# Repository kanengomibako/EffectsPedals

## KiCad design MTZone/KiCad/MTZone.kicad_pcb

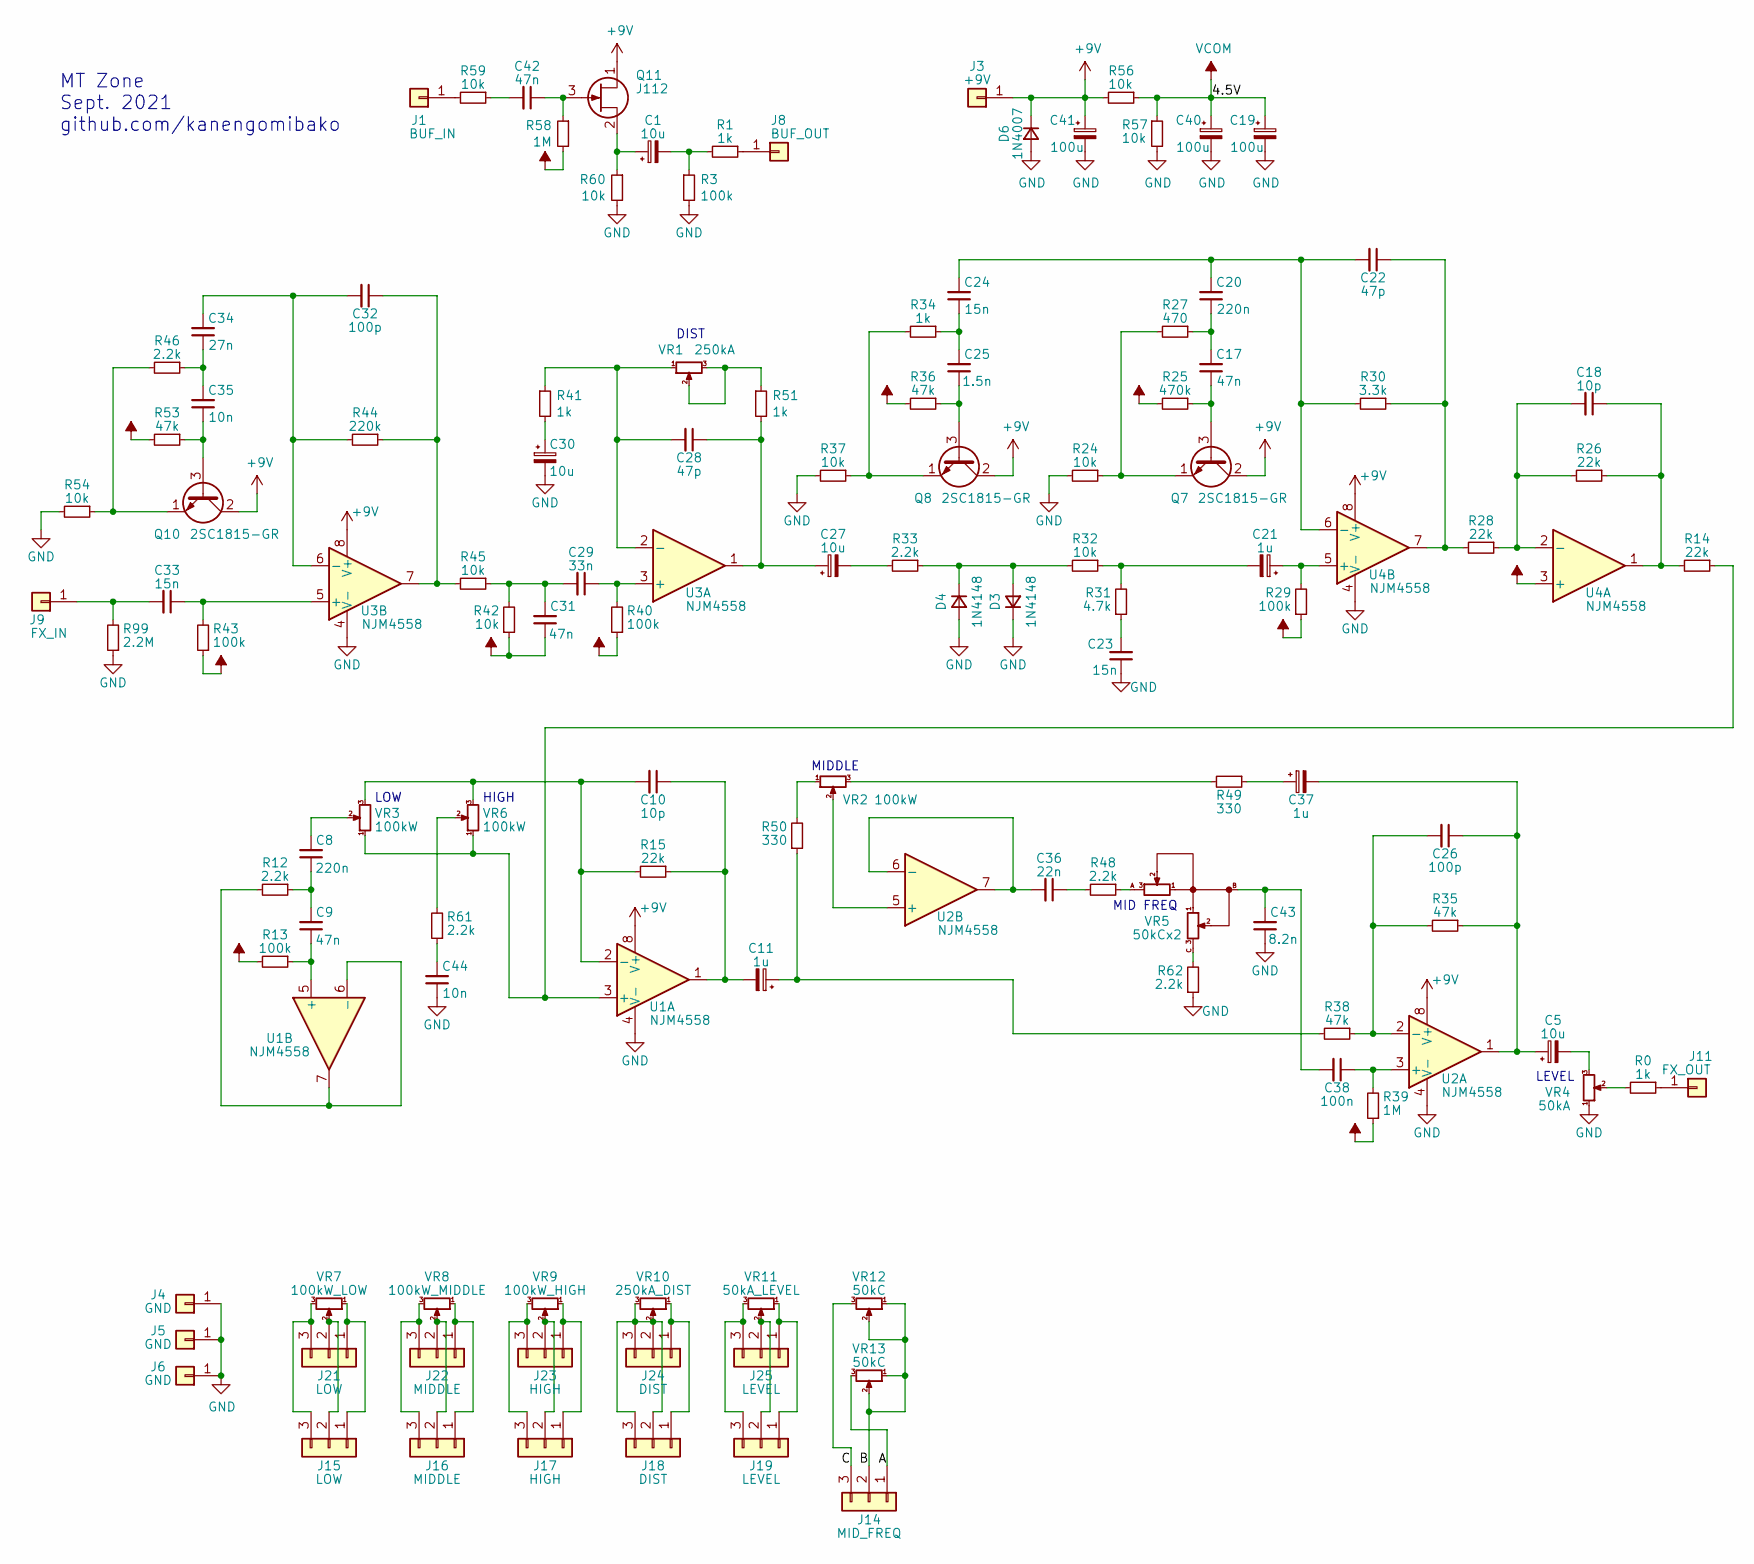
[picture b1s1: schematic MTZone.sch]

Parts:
C1, C5, C27, C30: 10u; my_C_D5.0mm_P2.50mm
C8, C20: 220n; my_C_Rect2_P5.00mm
C9, C17, C31, C42: 47n; my_C_Rect1_P5.00mm
C10, C18: 10p; my_C_Disc_P2.50mm
C11, C21, C37: 1u; my_C_D5.0mm_P2.50mm
C19, C40, C41: 100u; my_C_D5.0mm_P2.50mm
C22, C28: 47p; my_C_Disc_P2.50mm
C23, C24, C33: 15n; my_C_Rect1_P5.00mm
C25: 1.5n; my_C_Rect1_P5.00mm
C26, C32: 100p; my_C_Disc_P2.50mm
C29: 33n; my_C_Rect1_P5.00mm
C34: 27n; my_C_Rect1_P5.00mm
C35, C44: 10n; my_C_Rect1_P5.00mm
C36: 22n; my_C_Rect1_P5.00mm
C38: 100n; my_C_Rect1_P5.00mm
C43: 8.2n; my_C_Rect1_P5.00mm
D3, D4: 1N4148; my_D_P5.08mm_Horizontal
D6: 1N4007; my_D_P7.62mm
J1: BUF_IN; my_WirePad_0-8mmDrill
J3: +9V; my_WirePad_0-8mmDrill
J4, J5, J6: GND; my_WirePad_0-8mmDrill
J8: BUF_OUT; my_WirePad_0-8mmDrill
J9: FX_IN; my_WirePad_0-8mmDrill
J11: FX_OUT; my_WirePad_0-8mmDrill
J14: MID_FREQ; my_pot_5mm_smallPad
J15, J21: LOW; my_pot_5mm_smallPad
J16, J22: MIDDLE; my_pot_5mm_smallPad
J17, J23: HIGH; my_pot_5mm_smallPad
J18, J24: DIST; my_pot_5mm_smallPad
J19, J25: LEVEL; my_pot_5mm_smallPad
Q7, Q8, Q10: 2SC1815-GR; TO-92_Inline_Wide
Q11: J112; TO-92_Inline_Wide
R0, R1, R34, R41, R51: 1k; my_R_P7mm_Horizontal
R3, R13, R29, R40, R43: 100k; my_R_P7mm_Horizontal
R12, R33, R46, R48, R61, R62: 2.2k; my_R_P7mm_Horizontal
R14, R15, R26, R28: 22k; my_R_P7mm_Horizontal
R24, R32, R37, R42, R45, R54, R56, R57, R59, R60: 10k; my_R_P7mm_Horizontal
R25: 470k; my_R_P7mm_Horizontal
R27: 470; my_R_P7mm_Horizontal
R30: 3.3k; my_R_P7mm_Horizontal
R31: 4.7k; my_R_P7mm_Horizontal
R35, R36, R38, R53: 47k; my_R_P7mm_Horizontal
R39, R58: 1M; my_R_P7mm_Horizontal
R44: 220k; my_R_P7mm_Horizontal
R49, R50: 330; my_R_P7mm_Horizontal
R99: 2.2M; my_R_P7mm_Horizontal
U1, U2, U3, U4: NJM4558; DIP-8_W7.62mm
VR1: 250kA; my_pot_5mm
VR2, VR3, VR6: 100kW; my_pot_5mm
VR4: 50kA; my_pot_5mm
VR5: 50kCx2; my_pot_5mm
VR7: 100kW_LOW; my_pot_5mm_widePad
VR8: 100kW_MIDDLE; my_pot_5mm_widePad
VR9: 100kW_HIGH; my_pot_5mm_widePad
VR10: 250kA_DIST; my_pot_5mm_widePad
VR11: 50kA_LEVEL; my_pot_5mm_widePad
VR12, VR13: 50kC; my_pot_5mm_widePad

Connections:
+9V: C41.1, D6.1 (K), J3.1, Q7.2 (C), Q8.2 (C), Q10.2 (C), Q11.1 (D), R56.2, U1.8 (V+), U2.8 (V+), U3.8 (V+), U4.8 (V+)
/A: J14.1, VR13.3
/B: J14.2, VR12.1, VR12.2, VR13.1, VR13.2
/C: J14.3, VR12.3
GND: C19.2, C23.1, C30.2, C40.2, C41.2, C43.1, C44.1, D3.1 (K), D4.2 (A), D6.2 (A), J4.1, J5.1, J6.1, R3.2, R24.2, R37.2, R54.2, R57.2, R60.2, R62.1, R99.1, U1.4 (V-), U2.4 (V-), U3.4 (V-), U4.4 (V-), VR4.1
unnamed: C1.1, Q11.2 (S), R60.1
unnamed: C1.2, R1.2, R3.1
unnamed: C5.2, VR4.3
unnamed: C8.1, C9.2, R12.1
unnamed: C8.2, VR3.2
unnamed: C9.1, R13.1, U1.5 (+)
unnamed: C10.1, C11.2, R15.1, U1.1
unnamed: C10.2, R15.2, U1.2 (-), VR3.3, VR6.3
unnamed: C11.1, R38.2, R50.1
unnamed: C17.1, Q7.3 (B), R25.1
unnamed: C17.2, C20.1, R27.1
unnamed: C18.1, R14.2, R26.1, U4.1
unnamed: C18.2, R26.2, R28.1, U4.2 (-)
unnamed: C20.2, C22.2, C24.2, R30.2, U4.6 (-)
unnamed: C21.1, R29.2, U4.5 (+)
unnamed: C21.2, R31.2, R32.1
unnamed: C22.1, R28.2, R30.1, U4.7
unnamed: C23.2, R31.1
unnamed: C24.1, C25.2, R34.1
unnamed: C25.1, Q8.3 (B), R36.1
unnamed: C5.1, C26.1, C37.2, R35.1, U2.1
unnamed: C26.2, R35.2, R38.1, U2.2 (-)
unnamed: C27.1, C28.1, R51.2, U3.1
unnamed: C27.2, R33.2
unnamed: C28.2, R41.1, U3.2 (-), VR1.1
unnamed: C29.1, R40.2, U3.3 (+)
unnamed: C29.2, C31.2, R42.2, R45.1
unnamed: C30.1, R41.2
unnamed: C32.1, R44.1, R45.2, U3.7
unnamed: C32.2, C34.2, R44.2, U3.6 (-)
unnamed: C33.1, R43.2, U3.5 (+)
unnamed: C33.2, J9.1, R99.2
unnamed: C34.1, C35.2, R46.1
unnamed: C35.1, Q10.3 (B), R53.1
unnamed: C36.1, R48.2
unnamed: C36.2, U2.6 (-), U2.7
unnamed: C37.1, R49.1
unnamed: C38.1, R39.2, U2.3 (+)
unnamed: C38.2, C43.2, VR5.B
unnamed: C42.1, Q11.3 (G), R58.1
unnamed: C42.2, R59.1
unnamed: C44.2, R61.1
unnamed: D3.2 (A), D4.1 (K), R32.2, R33.1
unnamed: J1.1, R59.2
unnamed: J8.1, R1.1
unnamed: J11.1, R0.1
unnamed: J15.1, J21.1, VR7.1
unnamed: J15.2, J21.2, VR7.2
unnamed: J15.3, J21.3, VR7.3
unnamed: J16.1, J22.1, VR8.1
unnamed: J16.2, J22.2, VR8.2
unnamed: J16.3, J22.3, VR8.3
unnamed: J17.1, J23.1, VR9.1
unnamed: J17.2, J23.2, VR9.2
unnamed: J17.3, J23.3, VR9.3
unnamed: J18.1, J24.1, VR10.1
unnamed: J18.2, J18.3, J24.2, J24.3, VR10.2, VR10.3
unnamed: J19.1, J25.1, VR11.1
unnamed: J19.2, J25.2, VR11.2
unnamed: J19.3, J25.3, VR11.3
unnamed: Q7.1 (E), R24.1, R27.2
unnamed: Q8.1 (E), R34.2, R37.1
unnamed: Q10.1 (E), R46.2, R54.1
unnamed: R0.2, VR4.2
unnamed: R12.2, U1.6 (-), U1.7
unnamed: R14.1, U1.3 (+), VR3.1, VR6.1
unnamed: R48.1, VR5.A
unnamed: R49.2, VR2.3
unnamed: R50.2, VR2.1
unnamed: R51.1, VR1.2, VR1.3
unnamed: R61.2, VR6.2
unnamed: R62.2, VR5.C
unnamed: U2.5 (+), VR2.2
VCOM: C19.1, C31.1, C40.1, R13.2, R25.2, R29.1, R36.2, R39.1, R40.1, R42.1, R43.1, R53.2, R56.1, R57.1, R58.2, U4.3 (+)

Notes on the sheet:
MT Zone Sept. 2021 github.com/kanengomibako
HIGH
LOW
DIST
LEVEL
MIDDLE
MID FREQ

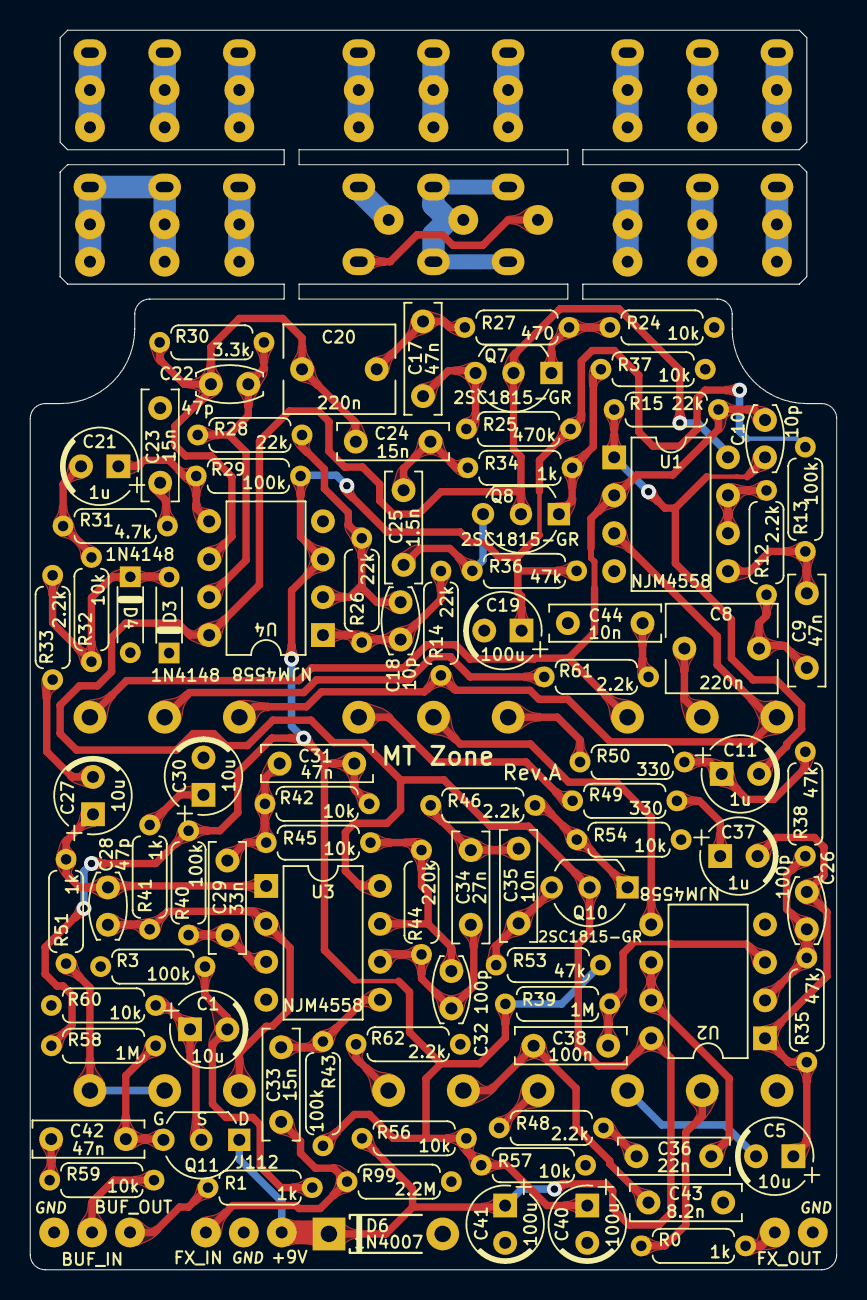
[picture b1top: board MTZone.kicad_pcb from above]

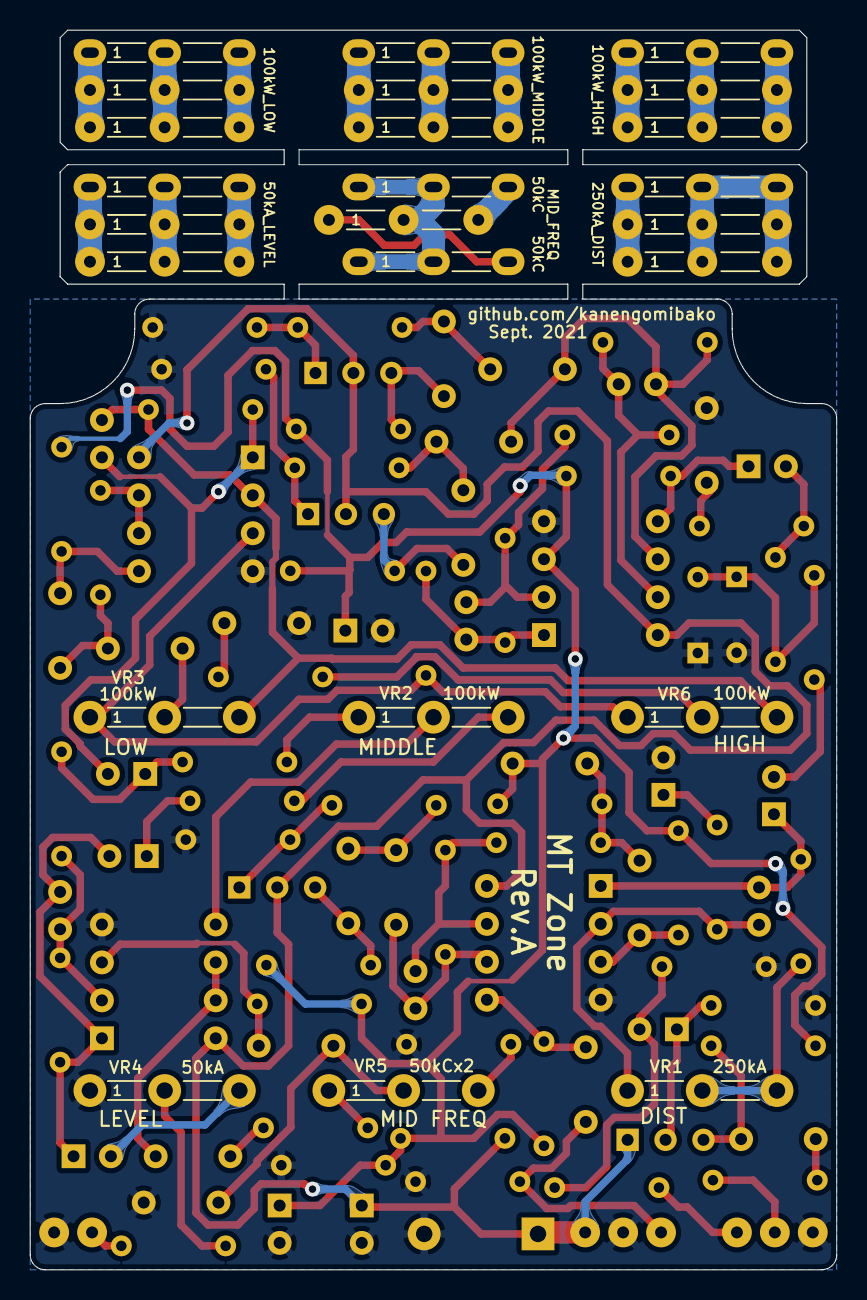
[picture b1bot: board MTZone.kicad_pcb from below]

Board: 2 copper layers, 54.0 x 83.0 mm, 120 parts (24 on the bottom side), 79 nets.

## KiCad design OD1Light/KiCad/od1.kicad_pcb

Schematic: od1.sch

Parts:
C1: 47n; C_0402_1005Metric
C2: 22n; C_0603_1608Metric
C3: 47p; C_0402_1005Metric
C4: 10n; C_0603_1608Metric
C5: 100n; C_0603_1608Metric
C6, C7, C8, C9: 10u; C_1206_3216Metric
D1, D2, D3, D4: MMSD4148; D_SOD-123
D5: LED; LED_D3.0mm
J1: VCC_IN_GND_OUT_LED-; PinHeader_1x05_P2.54mm_Vertical
R1, R8: 4.7k; R_0603_1608Metric
R2, R3: 1M; R_0603_1608Metric
R4: 33k; R_0603_1608Metric
R5: 18k; R_0603_1608Metric
R6: 1k; R_0603_1608Metric
R7: 100k; R_0603_1608Metric
RV1: 1MA; my_pot_5mm
RV2: 100kA; my_pot_5mm
U1: GS8632; MSOP-8_3x3mm_P0.65mm
U2: XC6221A332MR-G; SOT-23-5
U3: XC6221A182MR-G; SOT-23-5

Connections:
+1V8: C1.1, C4.1, C9.2, R3.2, RV2.1, U3.5 (OUT)
+3V3: C8.2, U1.8 (V+), U2.5 (OUT)
/INPUT: C2.2, J1.2, R2.1
/LED-: D5.1, J1.5
/OUTPUT: J1.4, R6.1, R7.1
/VCC: D4.2, J1.1, R8.2
GND: C7.1, C8.1, C9.1, J1.3, R2.2, R7.2, U1.4 (V-), U2.2 (GND), U3.2 (GND)
unnamed: C1.2, R1.1
unnamed: C2.1, R3.1, U1.5 (+)
unnamed: C3.1, D2.1, D3.2, R5.2, RV1.1, U1.7
unnamed: C3.2, D1.1, D2.2, R1.2, R4.2, U1.6 (-)
unnamed: C4.2, C5.2, R5.1
unnamed: C5.1, RV2.3
unnamed: C6.1, U1.1, U1.2 (-)
unnamed: C6.2, R6.2
unnamed: C7.2, D4.1, U2.1 (IN), U2.3 (EN), U3.1 (IN), U3.3 (EN)
unnamed: D1.2, D3.1
unnamed: D5.2, R8.1
unnamed: R4.1, RV1.2, RV1.3
unnamed: RV2.2, U1.3 (+)

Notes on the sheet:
BOSS OD-1 Over Drive (Light) May 2019 drugscore.blog.fc2.com
OVER DRIVE
LEVEL

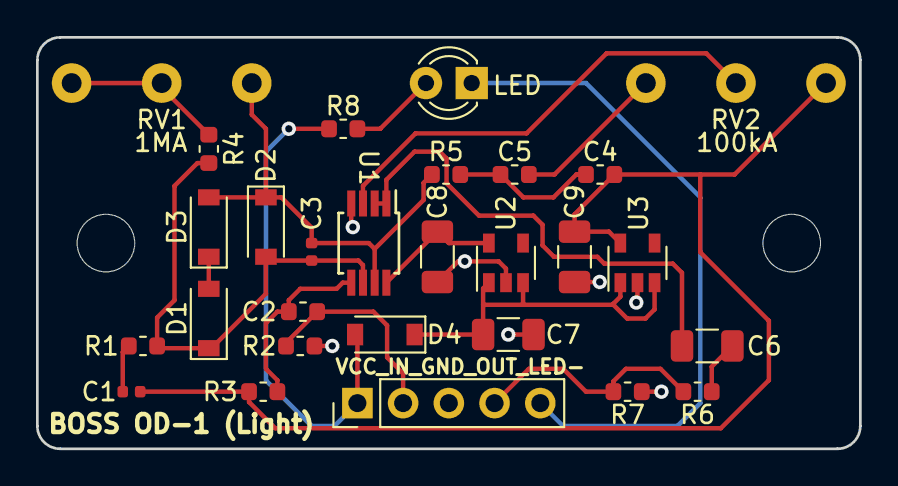
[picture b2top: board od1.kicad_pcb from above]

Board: 2 copper layers, 45.7 x 22.9 mm, 28 parts (0 on the bottom side), 20 nets.

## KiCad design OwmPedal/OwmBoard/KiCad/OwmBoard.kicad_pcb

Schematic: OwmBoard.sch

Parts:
C1, C3: 100n; my_C_3225(1210)_HandSoldering
C2, C4: 10n; my_C_1608(0603)_HandSoldering
C5, C6, C10, C11: 1n; my_C_1608(0603)_HandSoldering
C7, C8, C12, C13: 220p; my_C_1608(0603)_HandSoldering
C9, C14: 10u; my_CP_Elec_5
C15, C16, C17, C18: 20p; my_C_1608(0603)_HandSoldering
C19, C20: 2u2; my_C_2012(0805)_HandSoldering
C21, C41: 100u; my_C_D6.3mm_P2.50mm
C22, C23, C24, C25, C30, C31, C32, C33, C34, C35, C36, C37, C38, C39, C40, C42: 100n; my_C_1608(0603)_HandSoldering
C26, C27, C28, C29, C43: 10u; my_C_3216(1206)_HandSoldering
C44: (4u7); my_C_3216(1206)_HandSoldering
D1: LED; LED_D3.0mm
D2: 1N4007; D_DO-35_SOD27_P7.62mm_Horizontal
FB1: 330R; my_R_2012(0805)_HandSoldering
J1: LIN; my_SmallPad_0-8mmDrill
J2: RIN; my_SmallPad_0-8mmDrill
J3: LOUT; my_SmallPad_0-8mmDrill
J4: ROUT; my_SmallPad_0-8mmDrill
J5: C9(SDA); my_SmallPad_0-8mmDrill
J6: D2; my_SmallPad_0-8mmDrill
J7: C0; my_SmallPad_0-8mmDrill
J8: C1; my_SmallPad_0-8mmDrill
J9: C2; my_SmallPad_0-8mmDrill
J10: C3; my_SmallPad_0-8mmDrill
J11: C4; my_SmallPad_0-8mmDrill
J12: C5; my_SmallPad_0-8mmDrill
J13: C6; my_SmallPad_0-8mmDrill
J14: C7; my_SmallPad_0-8mmDrill
J16: C11; my_SmallPad_0-8mmDrill
J17, J18: 3.3VD; my_SmallPad_0-8mmDrill
J19, J20: DGND; my_SmallPad_0-8mmDrill
J21: A0; my_SmallPad_0-8mmDrill
J22: A1; my_SmallPad_0-8mmDrill
J23: A2; my_SmallPad_0-8mmDrill
J24: A3; my_SmallPad_0-8mmDrill
J25: A4; my_SmallPad_0-8mmDrill
J26: A5; my_SmallPad_0-8mmDrill
J27: A6; my_SmallPad_0-8mmDrill
J28: A7; my_SmallPad_0-8mmDrill
J29: A9; my_SmallPad_0-8mmDrill
J30: A10; my_SmallPad_0-8mmDrill
J31: A11; my_SmallPad_0-8mmDrill
J32: A12; my_SmallPad_0-8mmDrill
J33: SWD; my_SmallPad_0-8mmDrill
J34: SWC; my_SmallPad_0-8mmDrill
J35: B0; my_SmallPad_0-8mmDrill
J36: B1; my_SmallPad_0-8mmDrill
J37: B2; my_SmallPad_0-8mmDrill
J38: SWO; my_SmallPad_0-8mmDrill
J39: B4; my_SmallPad_0-8mmDrill
J40: B5; my_SmallPad_0-8mmDrill
J41: B6; my_SmallPad_0-8mmDrill
J42: B7; my_SmallPad_0-8mmDrill
J43: B8; my_SmallPad_0-8mmDrill
J44: B9; my_SmallPad_0-8mmDrill
J45: B10; my_SmallPad_0-8mmDrill
J46: B11; my_SmallPad_0-8mmDrill
J47: A15; my_SmallPad_0-8mmDrill
J48: A8(SCL); my_SmallPad_0-8mmDrill
J49, J51, J52: AGND; my_SmallPad_0-8mmDrill
J50: Vcc; my_SmallPad_0-8mmDrill
J53: NRST; my_SmallPad_0-8mmDrill
J54: C10; my_SmallPad_0-8mmDrill
J55: C12; my_SmallPad_0-8mmDrill
R1, R7, R38: 1k; my_R_2012(0805)_HandSoldering
R2, R8: 1M; my_R_1608(0603)_HandSoldering
R3, R4, R9, R10, R13, R14, R15, R16, R17, R18, R23, R24, R25, R26, R27, R28, R34, R36, R39, R41, R42: 10k; my_R_1608(0603)_HandSoldering
R5, R6, R11, R12, R21, R31: 100R; my_R_2012(0805)_HandSoldering
R19, R20, R29, R30: 2.2k; my_R_1608(0603)_HandSoldering
R22, R32, R43, R44: 100k; my_R_1608(0603)_HandSoldering
R33: 47k; my_R_1608(0603)_HandSoldering
R35, R45: 2.2M; my_R_1608(0603)_HandSoldering
R37, R40: (10k); my_R_1608(0603)_HandSoldering
TP1: ADC; my_TestPoint_1.2mm
TP2: LRCK; my_TestPoint_1.2mm
TP3: BCK; my_TestPoint_1.2mm
TP4: DAC; my_TestPoint_1.2mm
U1, U2, U3: OPA1678; SOIC-8_3.9x4.9mm_P1.27mm
U4: V4220M; my_SSOP-28_5.3x10.2mm_Pitch0.65mm
U5: STM32F405RGT6; my_LQFP-64_10x10_P0.5
U6, U8: 78L05; SOT-89-3
U7: 7805; my_TO-252-3
U9: 7833; my_TO-252-3
U10: 78L33; SOT-89-3
Y1: 12.288MHz; Crystal_SMD_HC49-SD
Y2: 8MHz; Crystal_SMD_HC49-SD

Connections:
+3V3: C29.1, C33.1, C36.1, C38.1, C39.1, C42.1, J17.1, J18.1, R37.1, R39.1, R40.1, U5.1, U5.13, U5.19, U5.32, U5.48, U5.64, U9.3
+5VA: C27.1, C31.1, U4.21, U7.3
+5VD: C28.1, C32.1, U4.6, U8.1 (OUT), U10.3 (IN)
+9V: C21.1, C22.1, C23.1, D2.1, FB1.2, J50.1, U6.3 (IN), U7.1
/+3.3VL: C35.1, C40.1, R34.1, U4.12, U4.13, U4.18, U10.1 (OUT)
/+5VAA: C26.1, C30.1, C34.1, C37.1, R41.2, U1.8 (V+), U2.8 (V+), U3.8 (V+), U6.1 (OUT)
/ADCDATA: R33.1, TP1.1, U4.8, U5.35
/BCK: TP3.1, U4.5, U5.34
/BIAS: C5.2, C6.2, C8.2, C10.2, C11.2, C13.2, C41.1, R2.2, R8.2, R17.2, R27.2, R41.1, R42.1, R43.1, R44.1, U1.3 (+), U2.3 (+)
/DACDATA: TP4.1, U4.9, U5.36
/LADC+: C2.1, R5.1, U4.20
/LADC-: C2.2, R6.1, U4.19
/LDAC+: R14.2, U4.25
/LDAC-: R13.2, U4.26
/LRCK: TP2.1, U4.4, U5.33
/RADC+: C4.1, R11.1, U4.17
/RADC-: C4.2, R12.1, U4.16
/RDAC+: R24.2, U4.24
/RDAC-: R23.2, U4.23
/RSTN: C43.1, R34.2, U4.27, U5.39
GNDA: C15.2, C16.2, C17.2, C18.2, C19.2, C20.2, C21.2, C22.2, C23.2, C24.2, C25.2, C26.2, C27.2, C28.2, C29.2, C30.2, C31.2, C32.2, C33.2, C34.2, C35.2, C36.2, C37.2, C38.2, C39.2, C40.2, C41.2, C42.2, C43.2, C44.2, D1.1, D2.2, J19.1, J20.1, J49.1, J51.1, J52.1, R22.2, R32.2, R33.2, R35.2, R36.2, R42.2, R43.2, R44.2, R45.2, U1.4 (V-), U2.4 (V-), U3.4 (V-), U4.1, U4.7, U4.10, U4.11, U4.14, U4.15, U4.22, U4.28, U5.12, U5.18, U5.63, U6.2 (GND), U7.2, U8.2 (GND), U9.2, U10.2 (GND)
unnamed: C1.1, R1.2
unnamed: C1.2, J1.1, R35.1
unnamed: C3.1, R7.2
unnamed: C3.2, J2.1, R45.1
unnamed: C5.1, R15.1, R18.2, R19.2
unnamed: C6.1, R16.1, R17.1, R20.2
unnamed: C7.1, C9.1, R18.1, U3.1
unnamed: C7.2, R19.1, U3.2 (-)
unnamed: C8.1, R20.1, U3.3 (+)
unnamed: C9.2, R21.2
unnamed: C10.1, R25.1, R28.2, R29.2
unnamed: C11.1, R26.1, R27.1, R30.2
unnamed: C12.1, C14.1, R28.1, U3.7
unnamed: C12.2, R29.1, U3.6 (-)
unnamed: C13.1, R30.1, U3.5 (+)
unnamed: C14.2, R31.2
unnamed: C15.1, U4.3, Y1.1
unnamed: C16.1, U4.2, Y1.2
unnamed: C17.1, U5.6, Y2.1
unnamed: C18.1, U5.5, Y2.2
unnamed: C19.1, U5.31
unnamed: C20.1, U5.47
unnamed: C24.1, C25.1, FB1.1, U8.3 (IN), U9.1
unnamed: C44.1, J46.1, U5.30
unnamed: D1.2, R38.1
unnamed: J3.1, R21.1, R22.1
unnamed: J4.1, R31.1, R32.1
unnamed: J5.1, R37.2, U5.40
unnamed: J6.1, U5.54
unnamed: J7.1, U5.8
unnamed: J8.1, U5.9
unnamed: J9.1, U5.10
unnamed: J10.1, U5.11
unnamed: J11.1, U5.24
unnamed: J12.1, U5.25
unnamed: J13.1, U5.37
unnamed: J14.1, U5.38
unnamed: J16.1, U5.52
unnamed: J21.1, U5.14
unnamed: J22.1, U5.15
unnamed: J23.1, U5.16
unnamed: J24.1, U5.17
unnamed: J25.1, U5.20
unnamed: J26.1, U5.21
unnamed: J27.1, U5.22
unnamed: J28.1, U5.23
unnamed: J29.1, U5.42
unnamed: J30.1, U5.43
unnamed: J31.1, U5.44
unnamed: J32.1, U5.45
unnamed: J33.1, U5.46
unnamed: J34.1, U5.49
unnamed: J35.1, U5.26
unnamed: J36.1, U5.27
unnamed: J37.1, U5.28
unnamed: J38.1, U5.55
unnamed: J39.1, U5.56
unnamed: J40.1, U5.57
unnamed: J41.1, U5.58
unnamed: J42.1, U5.59
unnamed: J43.1, U5.61
unnamed: J44.1, U5.62
unnamed: J45.1, U5.29
unnamed: J47.1, U5.50
unnamed: J48.1, R40.2, U5.41
unnamed: J53.1, R39.2, U5.7
unnamed: J54.1, U5.51
unnamed: J55.1, U5.53
unnamed: R1.1, R2.1, U1.5 (+)
unnamed: R3.1, R5.2, U1.6 (-), U1.7
unnamed: R3.2, R4.2, U1.2 (-)
unnamed: R4.1, R6.2, U1.1
unnamed: R7.1, R8.1, U2.5 (+)
unnamed: R10.1, R12.2, U2.1
unnamed: R9.2, R10.2, U2.2 (-)
unnamed: R9.1, R11.2, U2.6 (-), U2.7
unnamed: R13.1, R15.2
unnamed: R14.1, R16.2
unnamed: R23.1, R25.2
unnamed: R24.1, R26.2
unnamed: R36.1, U5.60
unnamed: R38.2, U5.2

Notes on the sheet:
Owm Board Rev.C May 2019 drugscore.blog.fc2.com

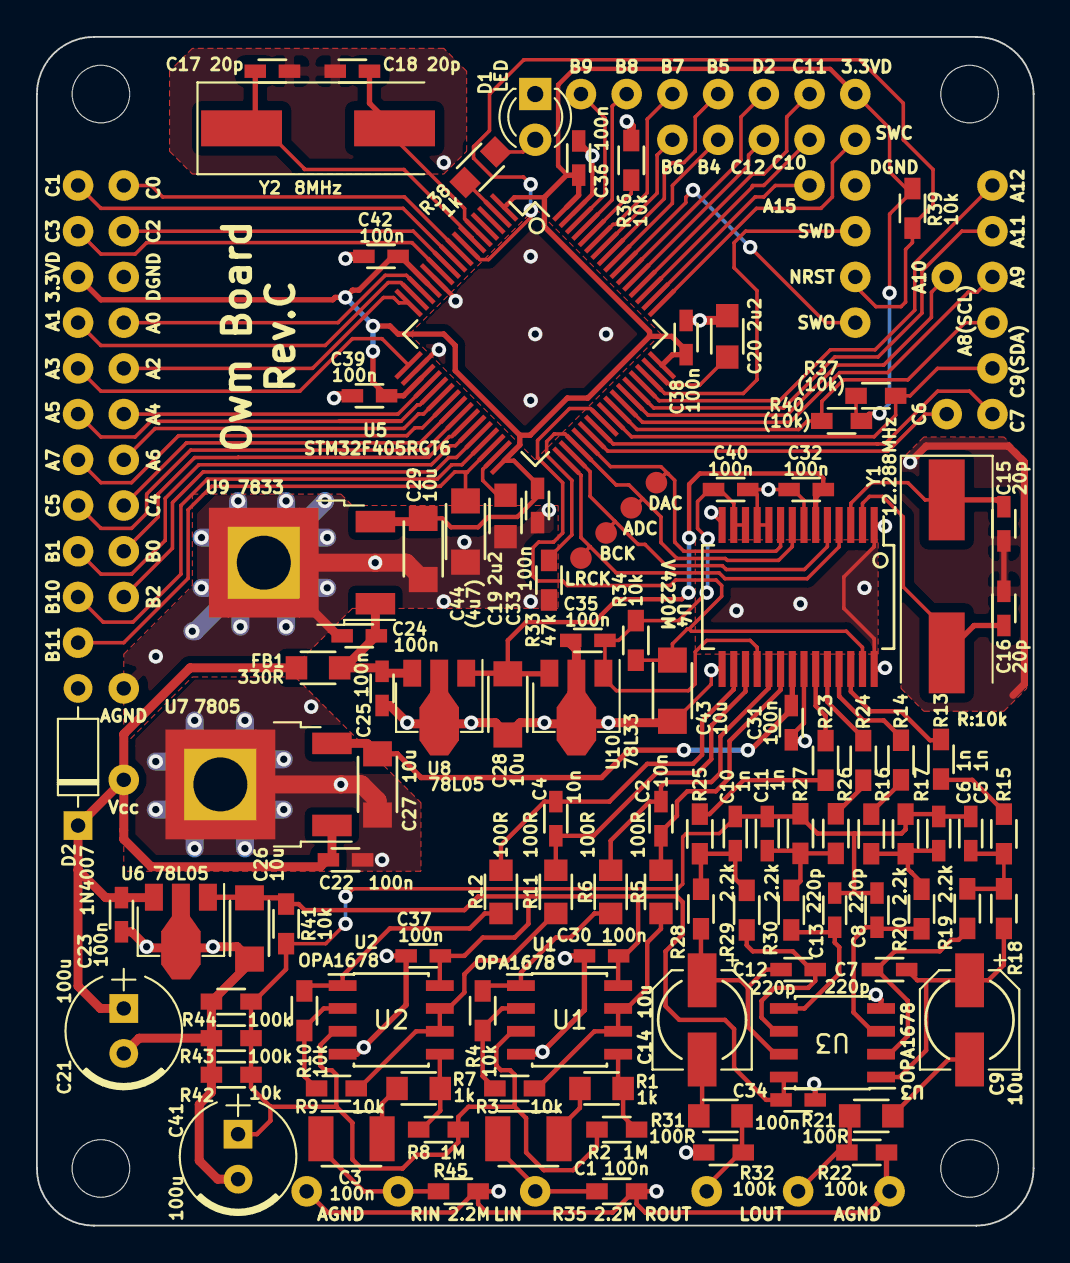
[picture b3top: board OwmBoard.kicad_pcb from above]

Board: 2 copper layers, 55.4 x 66.0 mm, 162 parts (0 on the bottom side), 103 nets.

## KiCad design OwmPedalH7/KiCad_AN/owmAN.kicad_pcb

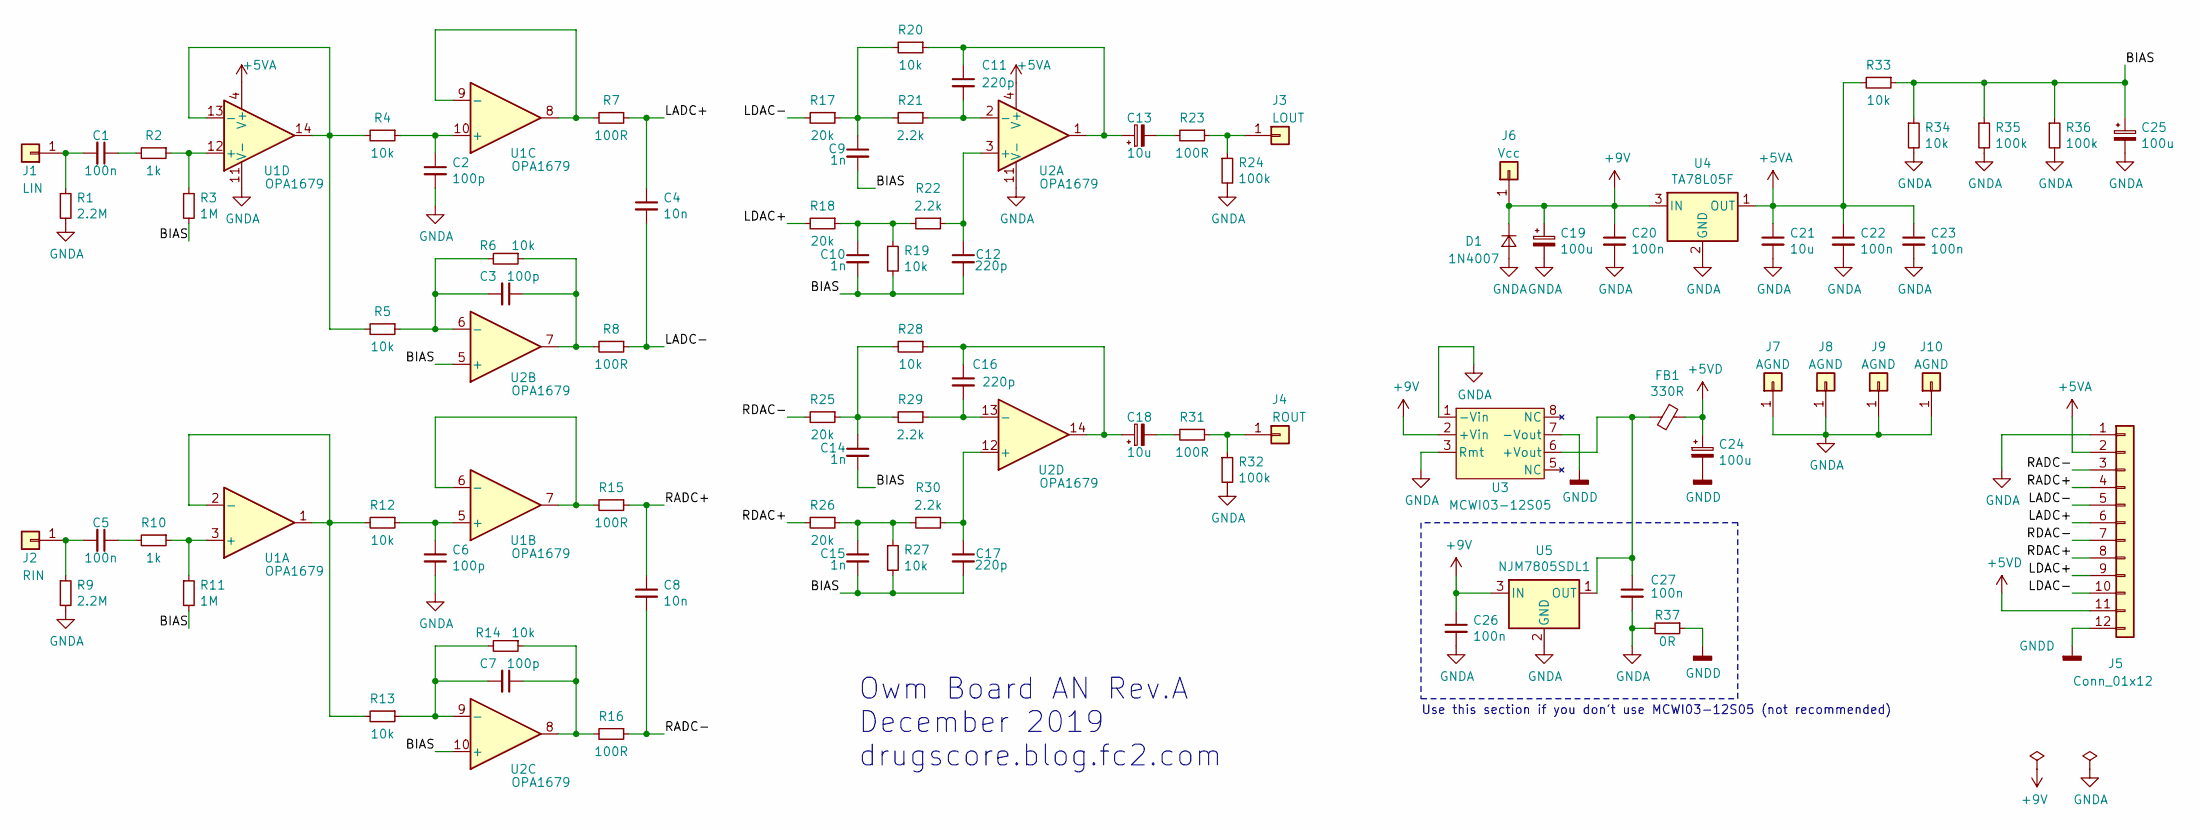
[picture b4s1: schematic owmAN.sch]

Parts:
C1, C5: 100n; my_C_3225(1210)_HandSoldering
C2, C3, C6, C7: 100p; my_C_1608(0603)_HandSoldering
C4, C8: 10n; my_C_1608(0603)_HandSoldering
C9, C10, C14, C15: 1n; my_C_1608(0603)_HandSoldering
C11, C12, C16, C17: 220p; my_C_1608(0603)_HandSoldering
C13, C18: 10u; my_C_Elec_5
C19, C24, C25: 100u; my_C_D6.3mm_P2.50mm
C20, C22, C23, C26, C27: 100n; my_C_1608(0603)_HandSoldering
C21: 10u; my_C_3216(1206)_HandSoldering
D1: 1N4007; D_DO-35_SOD27_P7.62mm_Horizontal
FB1: 330R; my_R_2012(0805)_HandSoldering
J1: LIN; my_SmallPad_0-8mmDrill
J2: RIN; my_SmallPad_0-8mmDrill
J3: LOUT; my_SmallPad_0-8mmDrill
J4: ROUT; my_SmallPad_0-8mmDrill
J5: Conn_01x12; PinHeader_1x12_P2.54mm_Vertical
J6: Vcc; my_SmallPad_0-8mmDrill
J7, J8, J9, J10: AGND; my_SmallPad_0-8mmDrill
R1, R9: 2.2M; my_R_1608(0603)_HandSoldering
R2, R10: 1k; my_R_2012(0805)_HandSoldering
R3, R11: 1M; my_R_1608(0603)_HandSoldering
R4, R5, R6, R12, R13, R14, R19, R20, R27, R28, R33, R34: 10k; my_R_1608(0603)_HandSoldering
R7, R8, R15, R16, R23, R31: 100R; my_R_2012(0805)_HandSoldering
R17, R18, R25, R26: 20k; my_R_1608(0603)_HandSoldering
R21, R22, R29, R30: 2.2k; my_R_1608(0603)_HandSoldering
R24, R32, R35, R36: 100k; my_R_1608(0603)_HandSoldering
R37: 0R; my_R_P7.62mm_Horizontal
U1, U2: OPA1679; my_TSSOP-14
U3: MCWI03-12S05
U4: TA78L05F; SOT-89-3
U5: NJM7805SDL1; my_TO-252-3

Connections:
+5VA: C21.1, C22.1, C23.1, J5.2, R33.2, U1.4 (V+), U2.4 (V+), U4.1 (OUT)
+5VD: C24.1, FB1.1, J5.11
+9V: C19.1, C20.1, C26.1, D1.1 (K), J6.1, U3.2 (+Vin), U4.3 (IN), U5.3 (IN)
/BIAS: C9.2, C10.2, C12.2, C14.2, C15.2, C17.2, C25.1, R3.2, R11.2, R19.2, R27.2, R33.1, R34.1, R35.1, R36.1, U2.5 (+), U2.10 (+)
/LADC+: C4.1, J5.6, R7.1
/LADC-: C4.2, J5.5, R8.1
/LDAC+: J5.9, R18.2
/LDAC-: J5.10, R17.2
/RADC+: C8.1, J5.4, R15.1
/RADC-: C8.2, J5.3, R16.1
/RDAC+: J5.8, R26.2
/RDAC-: J5.7, R25.2
GNDA: C2.2, C6.2, C19.2, C20.2, C21.2, C22.2, C23.2, C25.2, C26.2, C27.2, D1.2 (A), J5.1, J7.1, J8.1, J9.1, J10.1, R1.2, R9.2, R24.2, R32.2, R34.2, R35.2, R36.2, R37.2, U1.11 (V-), U2.11 (V-), U3.1 (-Vin), U3.3 (Rmt), U4.2 (GND), U5.2 (GND)
GNDD: C24.2, J5.12, R37.1, U3.7 (-Vout)
unnamed: C1.1, R2.2
unnamed: C1.2, J1.1, R1.1
unnamed: C2.1, R4.1, U1.10 (+)
unnamed: C3.1, R6.1, R8.2, U2.7
unnamed: C3.2, R5.1, R6.2, U2.6 (-)
unnamed: C5.1, R10.2
unnamed: C5.2, J2.1, R9.1
unnamed: C6.1, R12.1, U1.5 (+)
unnamed: C7.1, R14.1, R16.2, U2.8
unnamed: C7.2, R13.1, R14.2, U2.9 (-)
unnamed: C9.1, R17.1, R20.2, R21.2
unnamed: C10.1, R18.1, R19.1, R22.2
unnamed: C11.1, C13.1, R20.1, U2.1
unnamed: C11.2, R21.1, U2.2 (-)
unnamed: C12.1, R22.1, U2.3 (+)
unnamed: C13.2, R23.2
unnamed: C14.1, R25.1, R28.2, R29.2
unnamed: C15.1, R26.1, R27.1, R30.2
unnamed: C16.1, C18.1, R28.1, U2.14
unnamed: C16.2, R29.1, U2.13 (-)
unnamed: C17.1, R30.1, U2.12 (+)
unnamed: C18.2, R31.2
unnamed: C27.1, FB1.2, U3.6 (+Vout), U5.1 (OUT)
unnamed: J3.1, R23.1, R24.1
unnamed: J4.1, R31.1, R32.1
unnamed: R2.1, R3.1, U1.12 (+)
unnamed: R4.2, R5.2, U1.13 (-), U1.14
unnamed: R7.2, U1.8, U1.9 (-)
unnamed: R10.1, R11.1, U1.3 (+)
unnamed: R12.2, R13.2, U1.1, U1.2 (-)
unnamed: R15.2, U1.6 (-), U1.7

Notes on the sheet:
Owm Board AN Rev.A December 2019 drugscore.blog.fc2.com
Use this section if you don't use MCWI03-12S05 (not recommended)

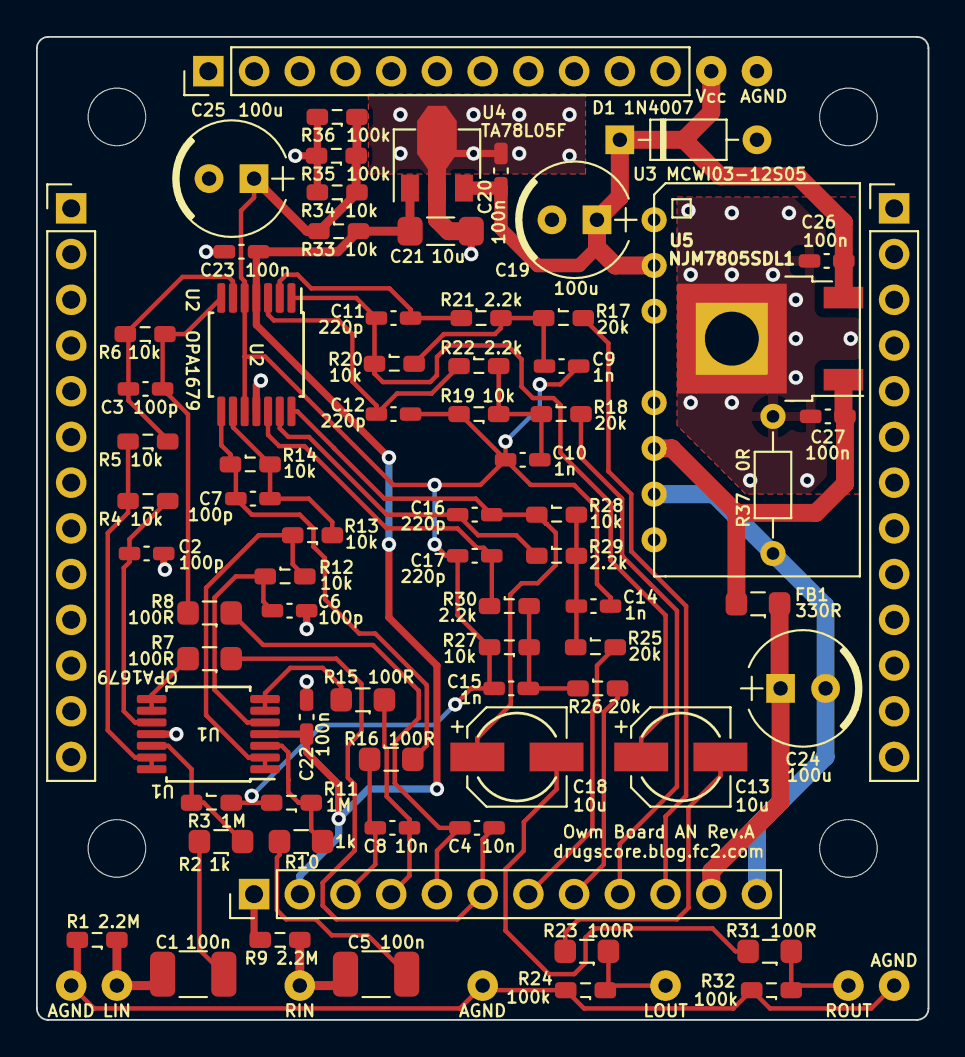
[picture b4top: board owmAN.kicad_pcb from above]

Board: 2 copper layers, 49.5 x 54.6 mm, 81 parts (0 on the bottom side), 45 nets.
